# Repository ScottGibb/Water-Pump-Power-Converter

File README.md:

# WaterPumpPowerConverter

# Summary
This repository contains a Switch Mode Power Supply(SMPS) used to power and control the water pumps developed for the various water fountains on Thingiverse. The SMPS module is based around the LM2596 chip. As well as this, a 3D printable case was designed using Fusion 360. The 3D Model of the PCB is shown below:

# Design
As for the design, I designed the circuit to use existing parts that I already had from previous projects; this is why it consists of all through-hole components. There are a lot of improvements that can be made to this design outlined below in the improvement section. As for the design, it was ordered through JLCPCB and is shown below:

# Improvements
There are a lot of improvements that can be undertaken for this PCB. First, there were a couple of issues during its manufacture and population. On the PCB itself, specifically in the top left corner, the board was malformed, resulting in a non-rectangular shape; this didn't change the functionality more than its aesthetics. As well as this, the LM2596 modules I ordered were originally clones, which meant that I had to remove the module from the board, resulting in damage to PCB pin holes, as seen in the picture above.

Layout Improvements include the following:

- Better Ground Stitching, at present, there is not much ground stitching between the top and bottom ground planes. This results in an uneven ground signal across the circuit, further resulting in power instability.
- LM2596 Through hole replacement, the layout is better with the SMT version as this allows the reduction of loop sizes, and thus a reduced EMI design can be created.
- Replacement of the unshielded inductor. Due to available parts, a non-shielded inductor was used. However, this resulted in increased EMI and thus created a noisy output voltage.

# Software Requirements:

The following software packages are required for this project:
- [Eagle](https://www.autodesk.co.uk/products/eagle/overview?term=1-YEAR&tab=subscription)
- [Fusion 360](https://www.autodesk.com/products/fusion-360/overview?term=1-YEAR&tab=subscription)

# Useful Links
- [Thingiverse Case](https://www.thingiverse.com/thing:4596788)
- [Case Exploded View](https://www.youtube.com/watch?v=MiPNAOpEotw)
- [JLCPCB](https://jlcpcb.com/)
- [Water Pump](https://www.thingiverse.com/thing:4594864)
- [Water Fountain](https://www.thingiverse.com/thing:4594351)

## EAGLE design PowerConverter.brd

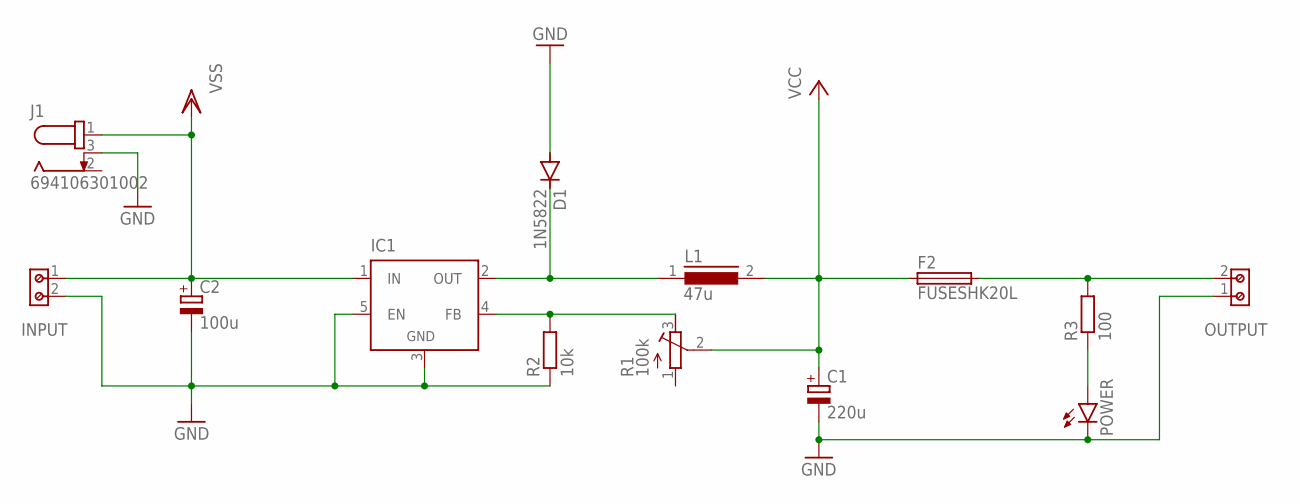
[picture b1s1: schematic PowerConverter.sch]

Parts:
C1: 220u; E3,5-8
C2: 100u; E3,5-8
D1: 1N5822; DO201-15
F2: FUSESHK20L; SHK20L
IC1: LM2596TV; TO220-51
INPUT: 691213510002
J1: 694106301002
L1: 47u; A26GFC
OUTPUT: 691213510002
POWER: LED5MM
R1: 100k; RTRIM3296W
R2: 10k; 0204/7
R3: 100; 0204/7

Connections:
GND: C1.-, C2.-, D1.A, IC1.3 (GND), IC1.5 (EN), INPUT.2, J1.2, J1.3, OUTPUT.1, POWER.K (C), R2.1
unnamed: POWER.A, R3.1
unnamed: D1.C, IC1.2 (OUT), L1.1
unnamed: IC1.4 (FB), R1.3 (E), R2.2
unnamed: F2.2A (2), OUTPUT.2, R3.2
VCC: C1.+, F2.1A (1), L1.2, R1.2 (S)
VSS: C2.+, IC1.1 (IN), INPUT.1, J1.1

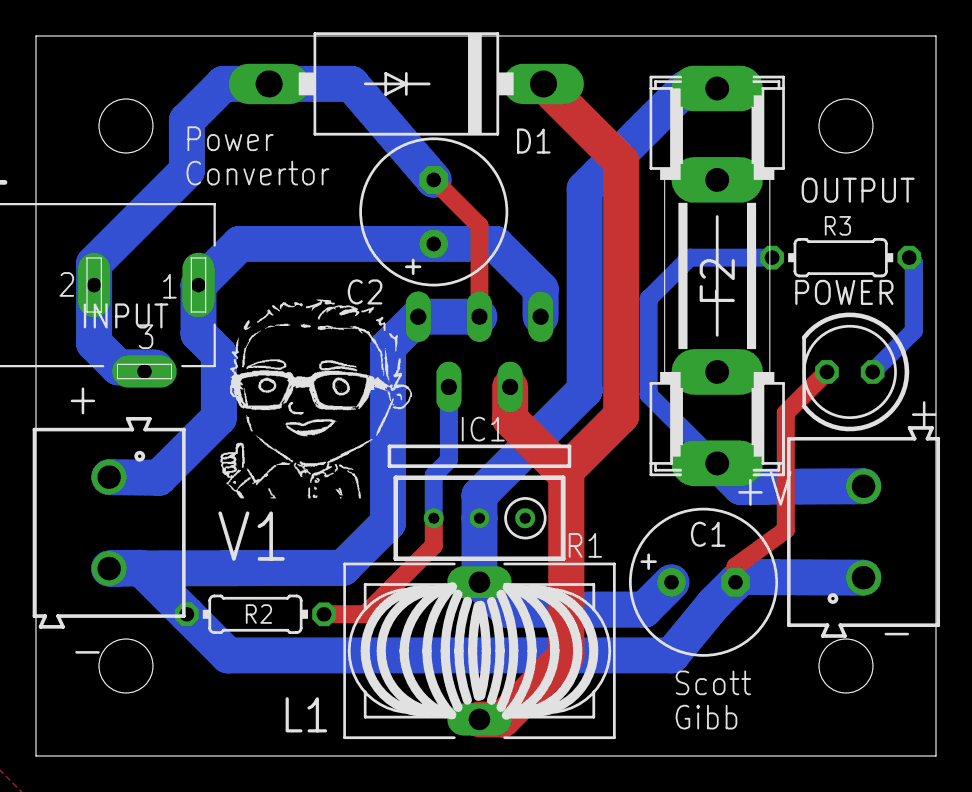
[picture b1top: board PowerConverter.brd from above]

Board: 6 copper layers, 50.0 x 40.0 mm, 13 parts (0 on the bottom side), 7 nets.

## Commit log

2020-09-14 Adding PCB Schematic and Layout Files
2020-09-27 Adding updated Files
2022-03-13 Create LICENSE
2022-09-27 3D CAD Render along with updated ReadMe
2022-09-27 Updating ReadMe
2022-09-27 Adding updated and cleaned repository
2022-09-27 Updating ReadMe and .gitignore
2022-09-28 Fixed Schematics Issues and added Logo to PCB

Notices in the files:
parts and their libraries:
Wurth_Connectors_WR-TBL Rising Cage Clam: Copyright: Würth Elektronik
